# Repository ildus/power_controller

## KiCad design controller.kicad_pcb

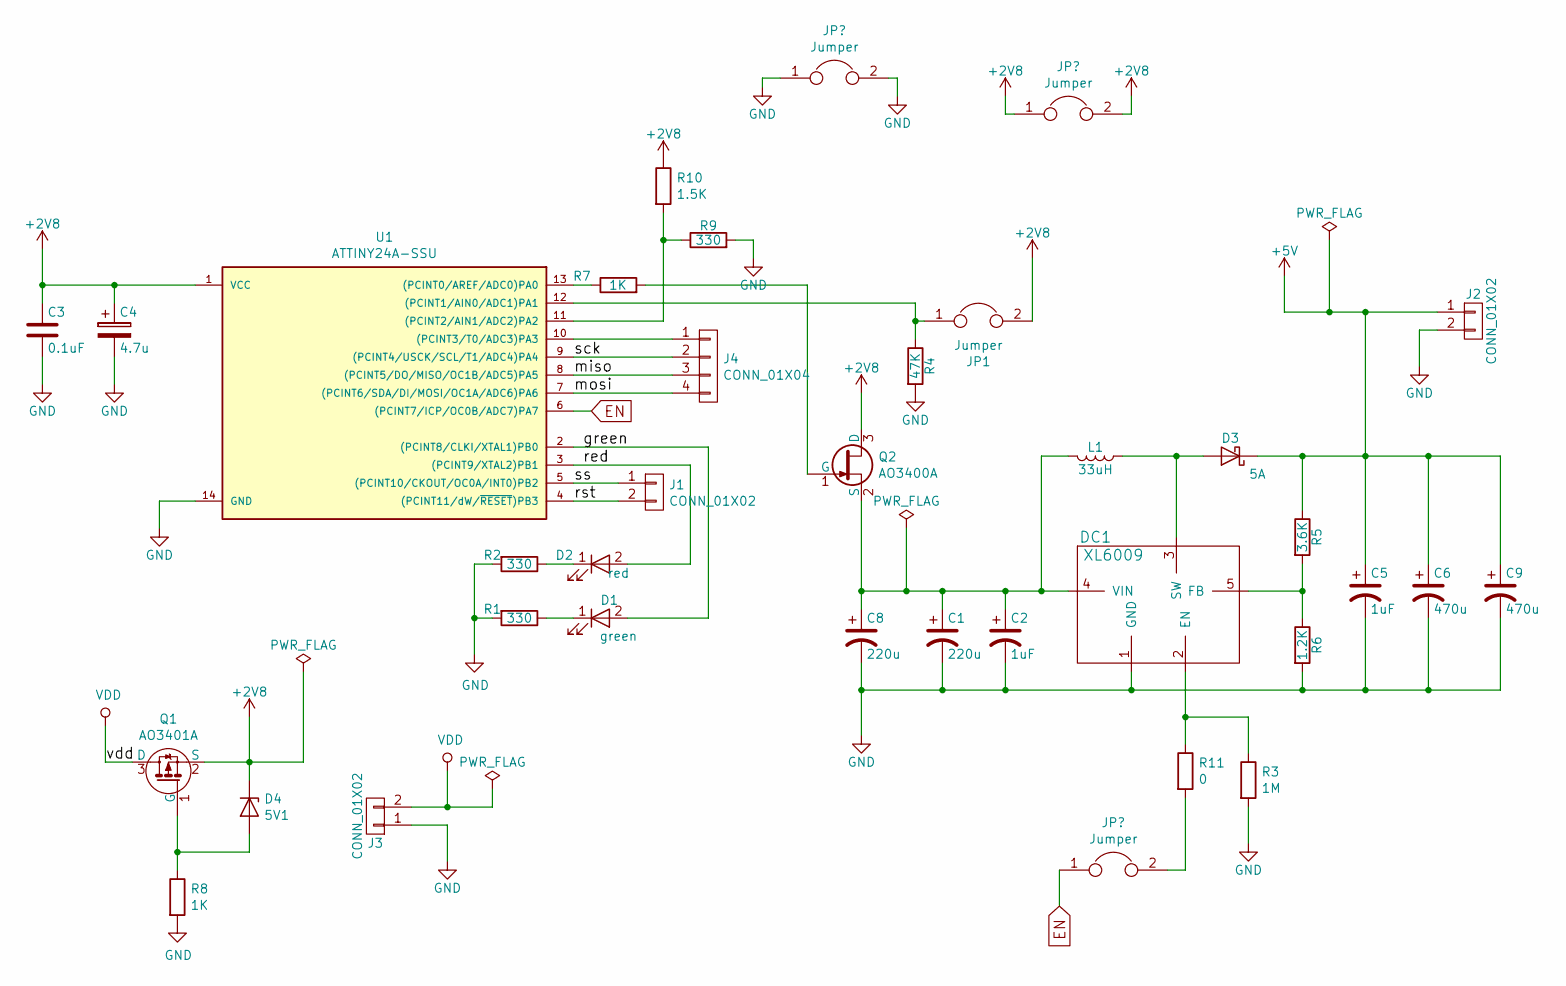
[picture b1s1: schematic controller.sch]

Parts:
C1, C8: 220u; CP_Elec_6.3x7.7
C2, C5: 1uF; C_0805
C3: 0.1uF; C_0805
C4: 4.7u; CP_Elec_4x5.7
C6, C9: 470u; CP_Tantalum_Case-V_EIA-7343-20_Hand
D1: green; LED_D1.8mm_W3.3mm_H2.4mm
D2: red; LED_D1.8mm_W3.3mm_H2.4mm
D3: 5A; D_DO-201_P12.70mm_Horizontal
D4: 5V1; SOT-23
DC1: XL6009; TO-263-5
J1, J2, J3: CONN_01X02; Molex_KK-6410-02_02x2.54mm_Straight
J4: CONN_01X04; Molex_KK-6410-04_04x2.54mm_Straight
JP1: Jumper; Molex_KK-6410-02_02x2.54mm_Straight
L1: 33uH; SELF-WE-PD-XXL
Q1: AO3401A; SOT-23
Q2: AO3400A; SOT-23
R1, R2, R9: 330; R_0805
R3: 1M; R_1206
R4: 47K; R_1206
R5: 3.6K; R_0805
R6: 1.2K; R_0805
R7, R8: 1K; R_0805
R10: 1.5K; R_0805
R11: 0; R_2512
U1: ATTINY24A-SSU; SOIC-14_3.9x8.7mm_Pitch1.27mm

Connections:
+2V8: C3.1, C4.1, D4.3 (K), JP1.2, Q1.2 (S), Q2.3 (D), R10.1, U1.1 (VCC); also elsewhere on the board
+5V: C5.1, C6.1, C9.1, D3.1 (K), J2.1, R5.1
/green: D1.2 (A), U1.2 ((PCINT8/CLKI/XTAL1)PB0)
/miso: J4.3, U1.8 ((PCINT5/DO/MISO/OC1B/ADC5)PA5)
/mosi: J4.4, U1.7 ((PCINT6/SDA/DI/MOSI/OC1A/ADC6)PA6)
/red: D2.2 (A), U1.3 ((PCINT9/XTAL2)PB1)
/rst: J1.2, U1.4 ((PCINT11/dW/~RESET~)PB3)
/sck: J4.2, U1.9 ((PCINT4/USCK/SCL/T1/ADC4)PA4)
/ss: J1.1, U1.5 ((PCINT10/CKOUT/OC0A/INT0)PB2)
EN: U1.6 ((PCINT7/ICP/OC0B/ADC7)PA7); also elsewhere on the board
GND: C1.2, C2.2, C3.2, C4.2, C5.2, C6.2, C8.2, C9.2, DC1.1 (GND), J2.2, J3.1, R1.2, R2.2, R3.2, R4.2, R6.2, R8.2, R9.2, U1.14 (GND); also elsewhere on the board
unnamed: C1.1, C2.1, C8.1, DC1.4 (VIN), L1.2, Q2.2 (S)
unnamed: D1.1 (K), R1.1
unnamed: D2.1 (K), R2.1
unnamed: D3.2 (A), DC1.3 (SW), L1.1
unnamed: D4.1 (A), Q1.1 (G), R8.1
unnamed: DC1.2 (EN), R3.1, R11.1
unnamed: DC1.5 (FB), R5.2, R6.1
unnamed: J4.1, U1.10 ((PCINT3/T0/ADC3)PA3)
unnamed: JP1.1, R4.1, U1.12 ((PCINT1/AIN0/ADC1)PA1)
unnamed 20: R11.2; also elsewhere on the board
unnamed: Q2.1 (G), R7.2
unnamed: R7.1, U1.13 ((PCINT0/AREF/ADC0)PA0)
unnamed: R9.1, R10.2, U1.11 ((PCINT2/AIN1/ADC2)PA2)
VDD: J3.2, Q1.3 (D)

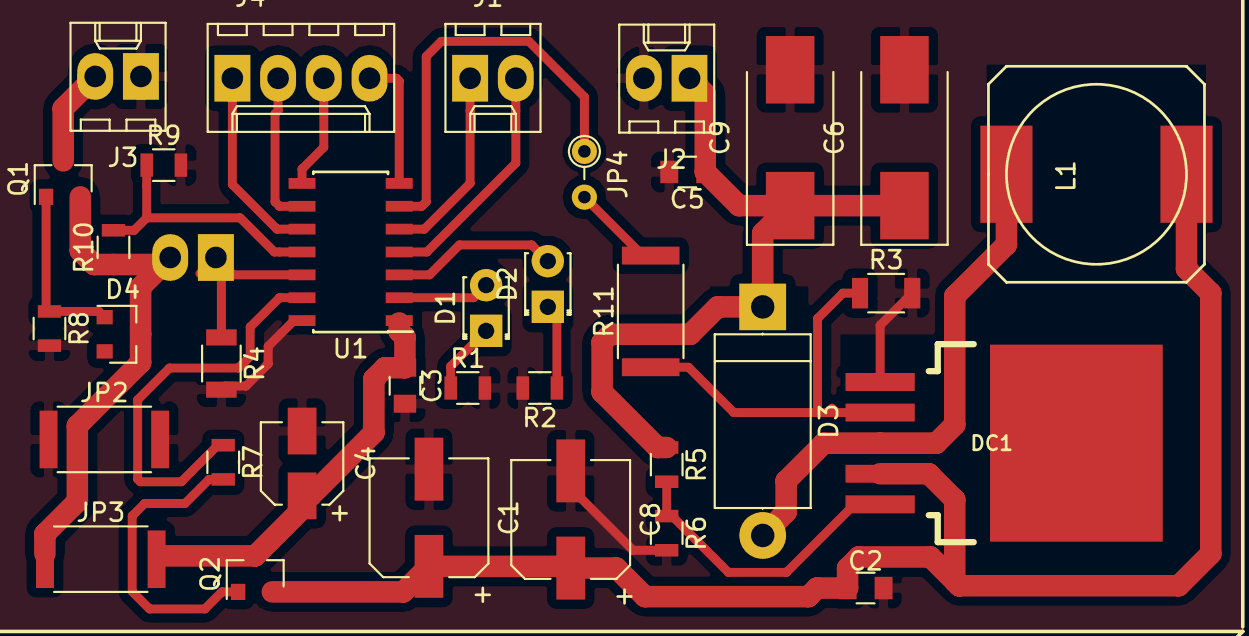
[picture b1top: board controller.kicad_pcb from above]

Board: 2 copper layers, 36 parts (1 on the bottom side), 25 nets.

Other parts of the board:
JP2, JP3: Jumper; R_2512
JP4: Jumper; R_Axial_DIN0204_L3.6mm_D1.6mm_P2.54mm_Vertical

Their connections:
+2V8: JP3.1, JP3.2; also elsewhere on the board
EN: JP4.1; also elsewhere on the board
GND: JP2.1, JP2.2; also elsewhere on the board
unnamed 20: JP4.2; also elsewhere on the board

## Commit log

2017-05-28 Initial
2017-06-03 Make last changes
2017-06-08 add circuit protection, refactor
2017-06-10 Remove ocsillators, add aref connection and pin for voltage check
2017-06-10 Add capacitor value
2017-07-18 Save changes
2017-07-20 Complete pcb
2017-07-21 change pcb
2017-07-22 Add last changes
